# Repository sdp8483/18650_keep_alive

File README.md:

# 18650 Battery Shield Keep Alive Circuit

The following circuit was designed to keep the 5V rail of a 18650 Battery Shield active even with no load attached. A comparator will "press" the tactile switch when the 5V rail goes below the 3V3 rail.

The circuit is built on a small one sided PCB that is attached to the battery shield using hot glue. Electrical connections are made using multi-strand wire.

Below is a photo of an unmodified 18650 Battery Shield. They may use keywords such as ESP32 or Raspberry Pi battery shield.

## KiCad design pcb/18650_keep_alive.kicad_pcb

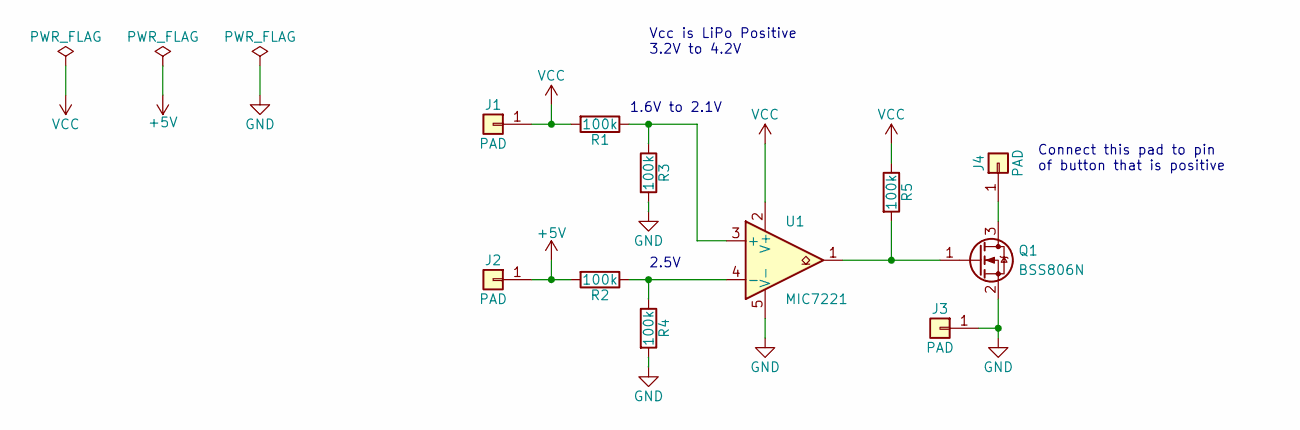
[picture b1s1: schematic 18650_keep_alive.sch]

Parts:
J1, J2, J3, J4: PAD; TestPoint_Pad_2.5x2.5mm
Q1: BSS806N; SOT-23
R1, R2, R3, R4, R5: 100k; R_0805_2012Metric
U1: MIC7221; SOT-23-5

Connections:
+5V: J2.1, R2.2
GND: J3.1, Q1.2 (S), R3.2, R4.2, U1.5 (V-)
unnamed: J4.1, Q1.3 (D)
unnamed: Q1.1 (G), R5.2, U1.1
unnamed: R1.1, R3.1, U1.3 (+)
unnamed: R2.1, R4.1, U1.4 (-)
VCC: J1.1, R1.2, R5.1, U1.2 (V+)

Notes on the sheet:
Vcc is LiPo Positive 3.2V to 4.2V
1.6V to 2.1V
2.5V
Connect this pad to pin of button that is positive

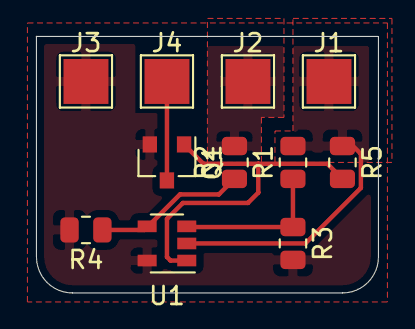
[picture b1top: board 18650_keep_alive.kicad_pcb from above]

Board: 2 copper layers, 19.0 x 14.2 mm, 11 parts (0 on the bottom side), 7 nets.

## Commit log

2020-10-23 init commit
2020-10-23 update cutout tool diameter
2020-10-24 round corners, set zero upper right
2020-10-24 update isolation cut to new orgin
2020-10-24 update with new orgin
2020-10-24 update with new orgin, round corners
2020-10-24 move gcode to inside gerber dir
2020-10-24 decrease cutting feedrate
2020-10-24 add images
2020-10-24 create project specific README
